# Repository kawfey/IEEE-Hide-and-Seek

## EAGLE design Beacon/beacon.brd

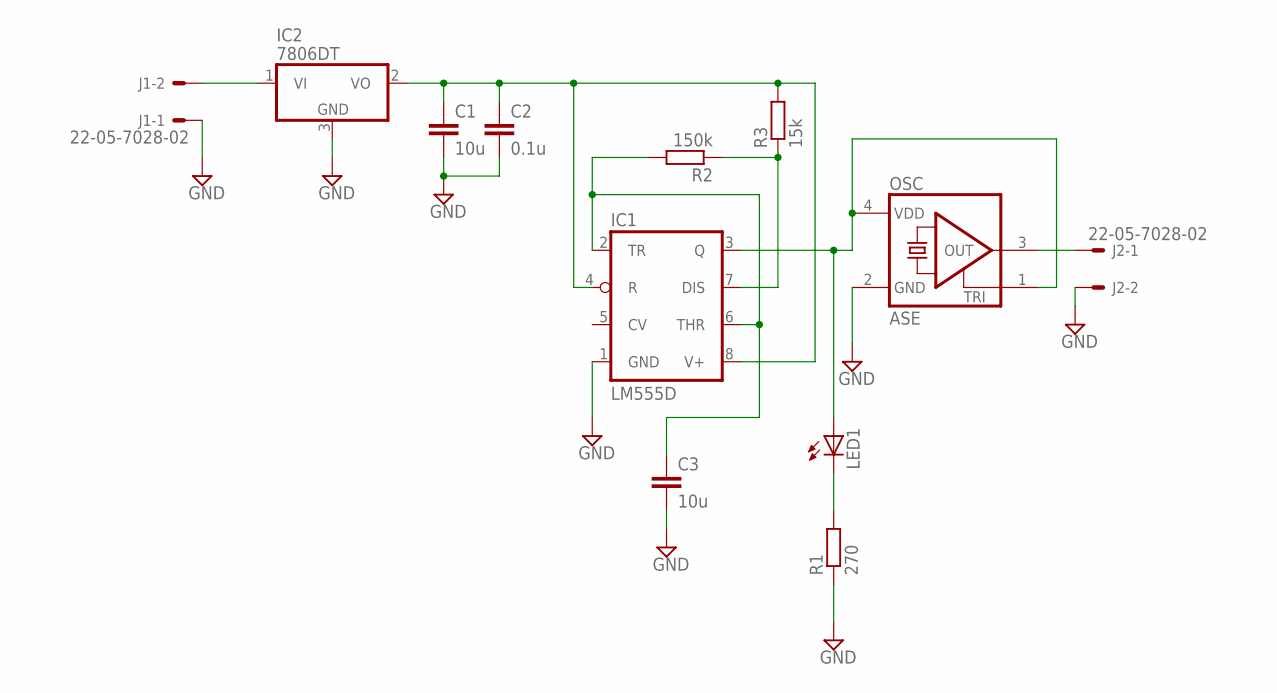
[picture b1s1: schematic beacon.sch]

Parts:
C1, C3: 10u; C0805
C2: 0.1u; C0805
IC1: LM555D; SO08
IC2: 7806DT; TO252
J1, J2: 22-05-7028-02; 7395-02
LED1: LED5MM
OSC: ASE
R1: 270; R0805
R2: 150k; R0805
R3: 15k; R0805

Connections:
GND: C1.2, C2.2, C3.2, IC1.1 (GND), IC2.3 (GND), J1.1, J2.2, OSC.2 (GND), R1.1
unnamed: C3.1, IC1.2 (TR), IC1.6 (THR), R2.2
unnamed: IC1.7 (DIS), R2.1, R3.1
unnamed: LED1.K (C), R1.2
unnamed: J2.1, OSC.3 (OUT)
unnamed: IC2.1 (VI), J1.2
VCC: C1.1, C2.1, IC1.4 (R), IC1.8 (V+), IC2.2 (VO), R3.2
VDD: IC1.3 (Q), LED1.A, OSC.1 (TRI), OSC.4 (VDD)

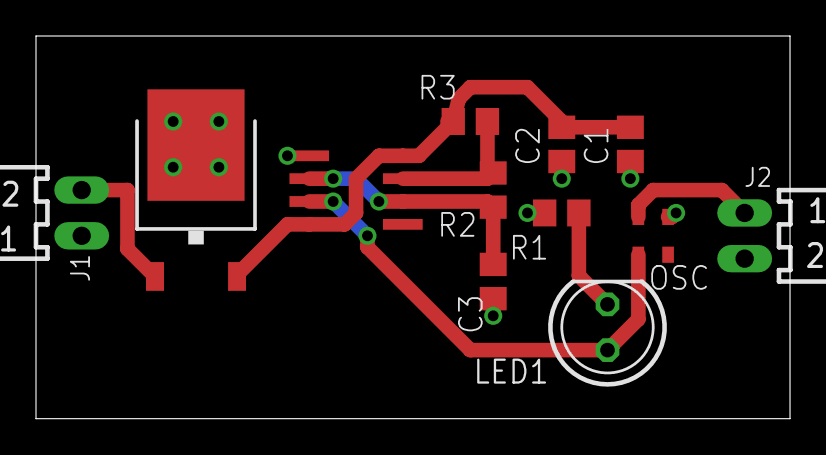
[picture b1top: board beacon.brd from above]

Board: 2 copper layers, 41.9 x 21.3 mm, 12 parts (0 on the bottom side), 8 nets.

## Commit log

2014-10-02 :circus_tent: Added .gitattributes
2014-10-02 Eagle Hardware files
    Added beacon hardware EAGLE files
